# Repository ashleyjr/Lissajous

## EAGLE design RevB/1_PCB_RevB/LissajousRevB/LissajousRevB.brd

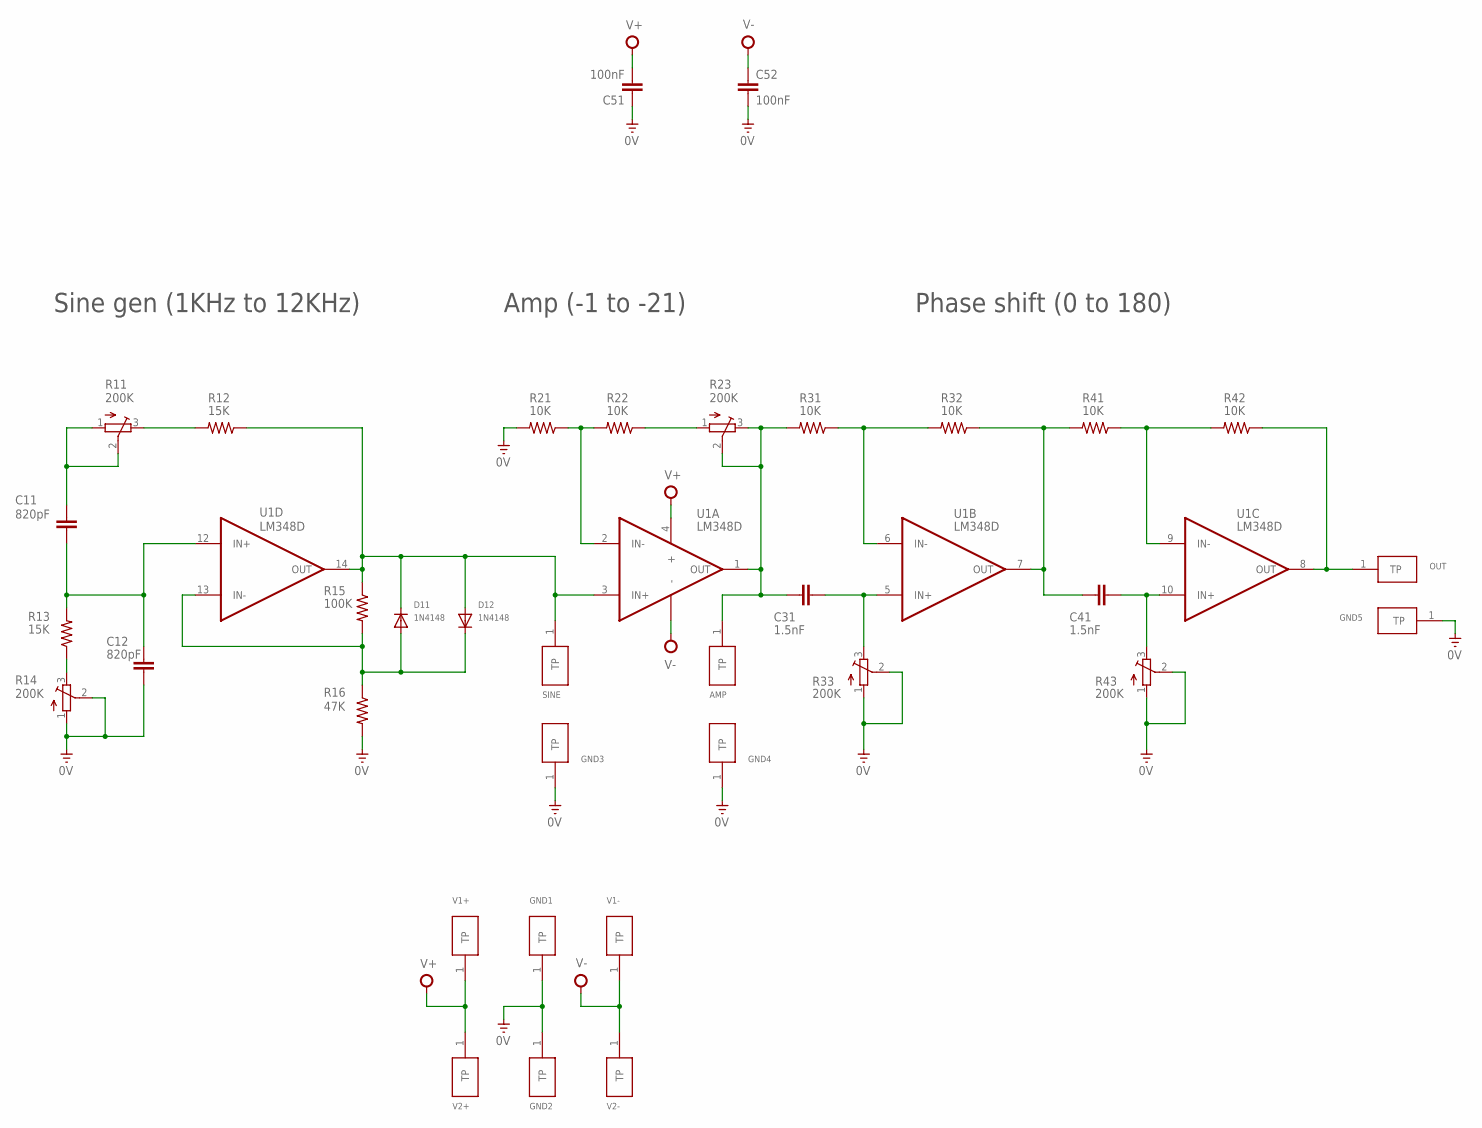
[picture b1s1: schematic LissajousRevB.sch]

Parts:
AMP: TESTPADS; TEST
C11, C12: 820pF; 0603-CAP
C31, C41: 1.5nF; 0603-CAP
C51, C52: 100nF; 0603-CAP
D11, D12: 1N4148; SMADIODE
GND1, GND2, GND3, GND4, GND5: TESTPADS; TEST
OUT: TESTPADS; TEST
R11, R14, R23, R33, R43: 200K; TC33X
R12, R13: 15K; 0603-RES
R15: 100K; 0603-RES
R16: 47K; 0603-RES
R21, R22, R31, R32, R41, R42: 10K; 0603-RES
SINE: TESTPADS; TEST
U1: LM348D; SOIC127P600X175-14N
V1+, V1-, V2+, V2-: TESTPADS; TEST

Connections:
0V: C12.1, C51.1, C52.2, GND1.1, GND2.1, GND3.1, GND4.1, GND5.1, R14.1 (A), R14.2 (S), R16.2, R21.2, R33.1 (A), R33.2 (S), R43.1 (A), R43.2 (S)
unnamed: R11.3 (E), R12.2
unnamed: R13.1, R14.3 (E)
unnamed: D11.A, D12.C, R15.2, R16.1, U1.13 (IN-)
unnamed: C11.2, R11.1 (A), R11.2 (S)
unnamed: R22.1, R23.1 (A)
unnamed: C11.1, C12.2, R13.2, U1.12 (IN+)
unnamed: R21.1, R22.2, U1.2 (IN-)
unnamed: R31.1, R32.2, U1.6 (IN-)
unnamed: C31.1, R33.3 (E), U1.5 (IN+)
unnamed: AMP.1, C31.2, R23.2 (S), R23.3 (E), R31.2, U1.1 (OUT)
unnamed: R41.1, R42.2, U1.9 (IN-)
unnamed: C41.1, R43.3 (E), U1.10 (IN+)
unnamed: OUT.1, R42.1, U1.8 (OUT)
unnamed: C41.2, R32.1, R41.2, U1.7 (OUT)
SINE: D11.C, D12.A, R12.1, R15.1, SINE.1, U1.3 (IN+), U1.14 (OUT)
V+: C51.2, U1.4 (+), V1+.1, V2+.1
V-: C52.1, U1.11 (-), V1-.1, V2-.1

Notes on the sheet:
Sine gen (1KHz to 12KHz)
Amp (-1 to -21)
Phase shift (0 to 180)

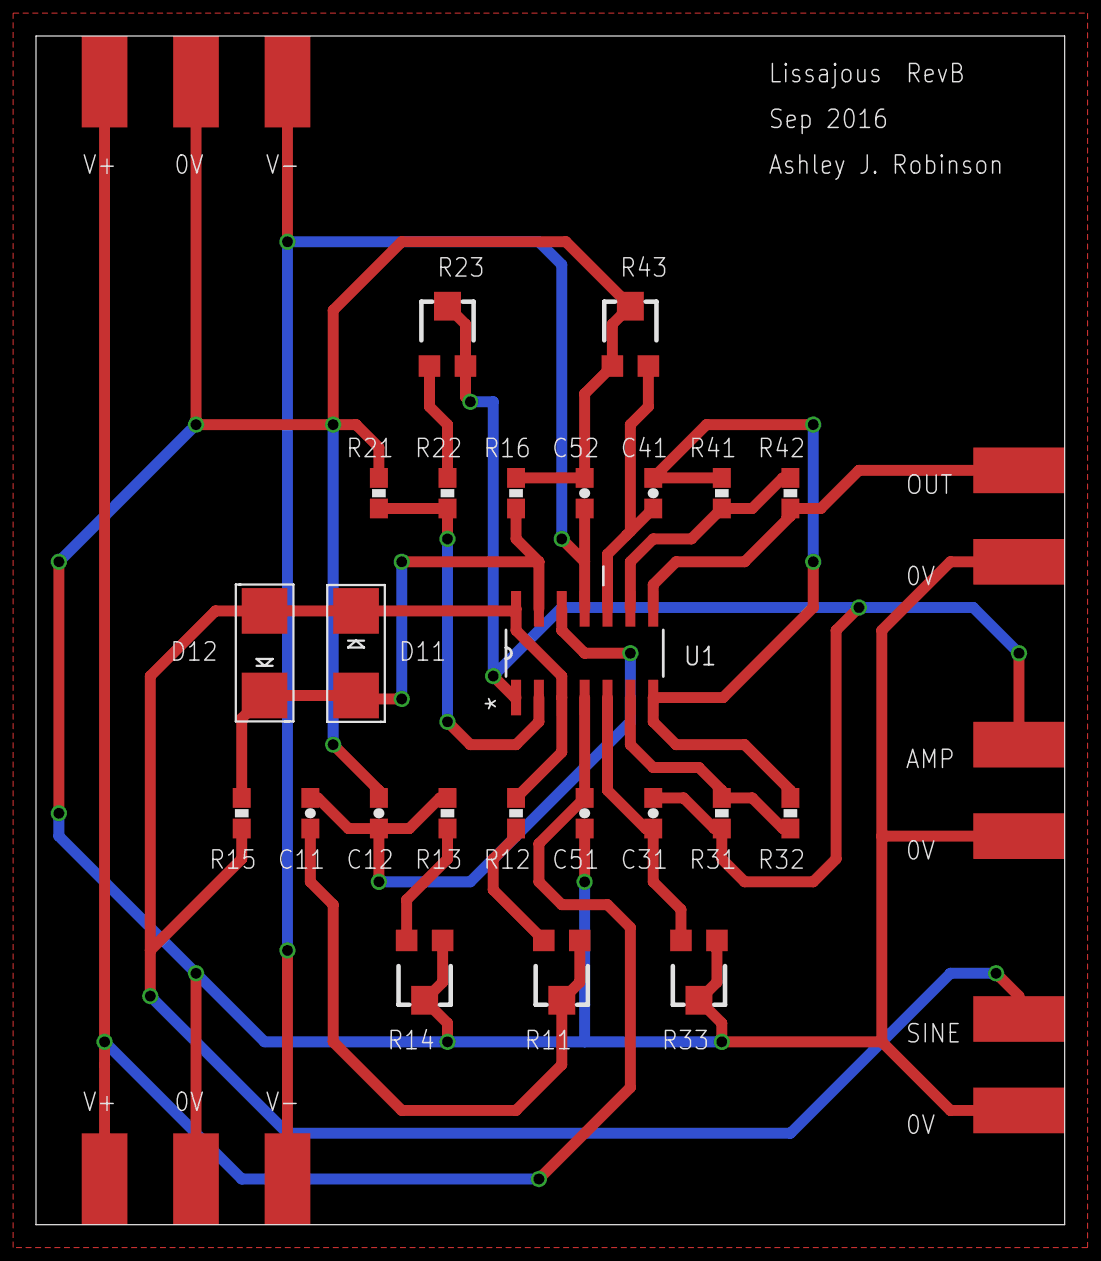
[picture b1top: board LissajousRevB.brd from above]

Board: 2 copper layers, 57.1 x 66.0 mm, 36 parts (0 on the bottom side), 18 nets.

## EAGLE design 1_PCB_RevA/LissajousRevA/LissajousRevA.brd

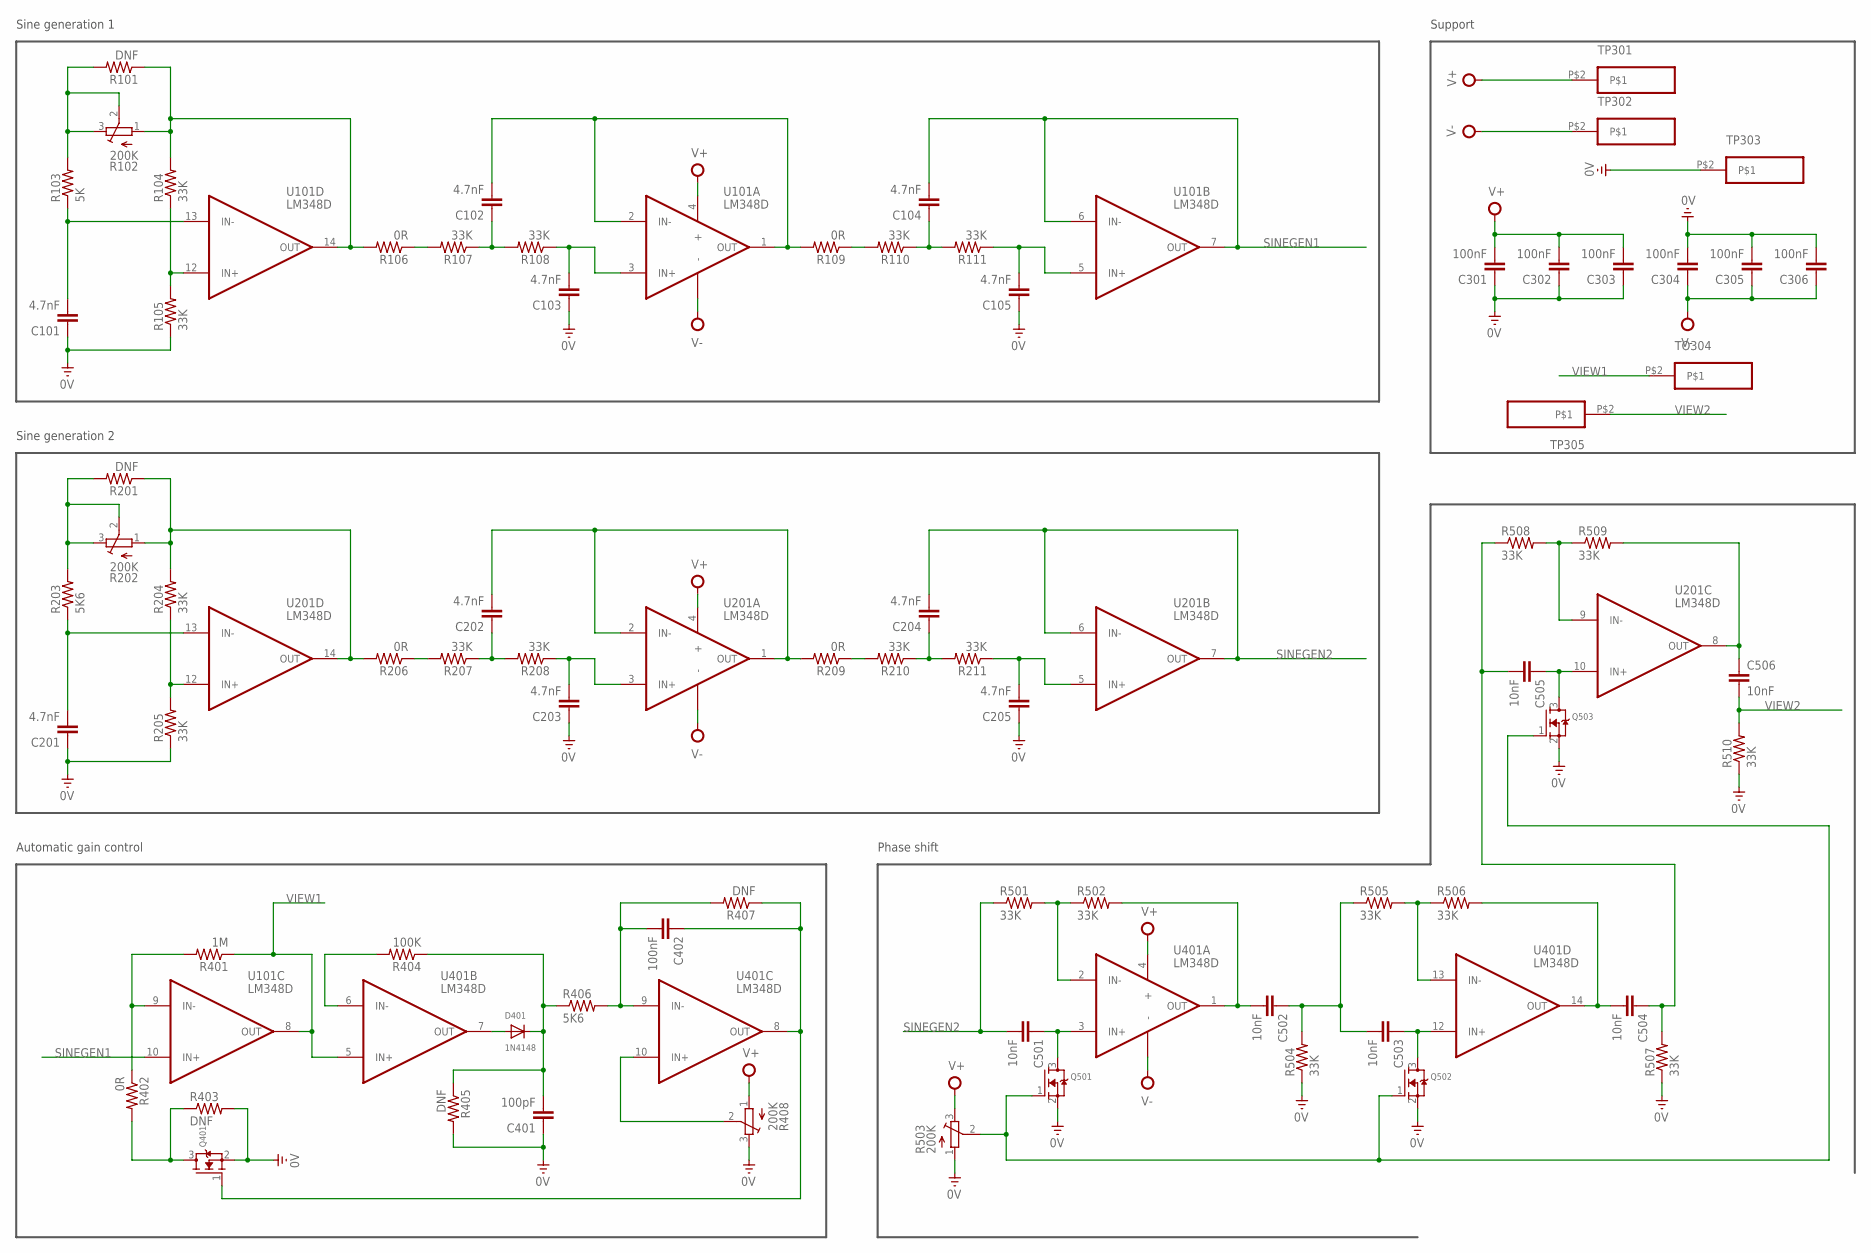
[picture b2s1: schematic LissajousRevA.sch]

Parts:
C101, C102, C103, C104, C105, C201, C202, C203, C204, C205: 4.7nF; 0603-CAP
C301, C302, C303, C304, C305, C306, C402: 100nF; 0603-CAP
C401: 100pF; 0603-CAP
C501, C502, C503, C504, C505, C506: 10nF; 0603-CAP
D401: 1N4148; SMADIODE
Q401, Q501, Q502, Q503: MOSFET-NREFLOW; SOT23
R101, R201, R403, R405, R407: DNF; 0603-RES
R102, R202, R408, R503: 200K; TC33X
R103: 5K; 0603-RES
R104, R105, R107, R108, R110, R111, R204, R205, R207, R208, R210, R211, R501, R502, R504, R505, R506, R507, R508, R509, R510: 33K; 0603-RES
R106, R109, R206, R209, R402: 0R; 0603-RES
R203, R406: 5K6; 0603-RES
R401: 1M; 0603-RES
R404: 100K; 0603-RES
TO304: PAD
TP301, TP302, TP303, TP305: PAD
U101, U201, U401: LM348D; SOIC127P600X175-14N

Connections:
0V: C101.1, C103.1, C105.1, C201.1, C203.1, C205.1, C301.1, C302.1, C303.1, C304.2, C305.2, C306.2, C401.1, Q401.2 (S), Q501.2 (S), Q502.2 (S), Q503.2 (S), R105.1, R205.1, R403.2, R405.2, R408.3 (E), R503.1 (A), R504.1, R507.1, R510.1, TP303.P$2
unnamed: C101.2, R103.1, U101.13 (IN-)
unnamed: R104.1, R105.2, U101.12 (IN+)
unnamed: R106.1, R107.2
unnamed: R101.2, R102.2 (S), R102.3 (E), R103.2
unnamed: C103.2, R108.1, U101.3 (IN+)
unnamed: C102.1, R107.1, R108.2
unnamed: R101.1, R102.1 (A), R104.2, R106.2, U101.14 (OUT)
unnamed: C102.2, R109.2, U101.1 (OUT), U101.2 (IN-)
unnamed: R204.1, R205.2, U201.12 (IN+)
unnamed: C201.2, R203.1, U201.13 (IN-)
unnamed: C105.2, R111.1, U101.5 (IN+)
unnamed: C104.1, R110.1, R111.2
unnamed: R401.2, R402.1, U101.9 (IN-)
unnamed: R109.1, R110.2
unnamed: R201.1, R202.1 (A), R204.2, R206.2, U201.14 (OUT)
unnamed: C203.2, R208.1, U201.3 (IN+)
unnamed: C202.1, R207.1, R208.2
unnamed: C205.2, R211.1, U201.5 (IN+)
unnamed: C204.1, R210.1, R211.2
unnamed: C501.1, Q501.3 (D), U401.3 (IN+)
unnamed: C202.2, R209.2, U201.1 (OUT), U201.2 (IN-)
unnamed: R206.1, R207.2
unnamed: R209.1, R210.2
unnamed: R201.2, R202.2 (S), R202.3 (E), R203.2
unnamed: C402.2, R406.2, R407.2, U401.9 (IN-)
unnamed: R501.2, R502.1, U401.2 (IN-)
unnamed: R404.2, U401.6 (IN-)
unnamed: D401.A, U401.7 (OUT)
unnamed: C502.1, C503.2, R504.2, R505.1
unnamed: C401.2, D401.C, R404.1, R405.1, R406.1
unnamed: Q401.3 (D), R402.2, R403.1
unnamed: C402.1, Q401.1 (G), R407.1, U401.8 (OUT)
unnamed: C502.2, R502.2, U401.1 (OUT)
unnamed: R408.2 (S), U401.10 (IN+)
unnamed: C503.1, Q502.3 (D), U401.12 (IN+)
unnamed: R505.2, R506.1, U401.13 (IN-)
unnamed: Q501.1 (G), Q502.1 (G), Q503.1 (G), R503.2 (S)
unnamed: C504.2, R506.2, U401.14 (OUT)
unnamed: R508.2, R509.1, U201.9 (IN-)
unnamed: C504.1, C505.2, R507.2, R508.1
unnamed: C505.1, Q503.3 (D), U201.10 (IN+)
unnamed: C506.1, R509.2, U201.8 (OUT)
SINEGEN1: C104.2, U101.6 (IN-), U101.7 (OUT), U101.10 (IN+)
SINEGEN2: C204.2, C501.2, R501.1, U201.6 (IN-), U201.7 (OUT)
V+: C301.2, C302.2, C303.2, R408.1 (A), R503.3 (E), TP301.P$2, U101.4 (+), U201.4 (+), U401.4 (+)
V-: C304.1, C305.1, C306.1, TP302.P$2, U101.11 (-), U201.11 (-), U401.11 (-)
VIEW1: R401.1, TO304.P$2, U101.8 (OUT), U401.5 (IN+)
VIEW2: C506.2, R510.2, TP305.P$2

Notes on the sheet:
Sine generation 1
Sine generation 2
Support
Automatic gain control
Phase shift

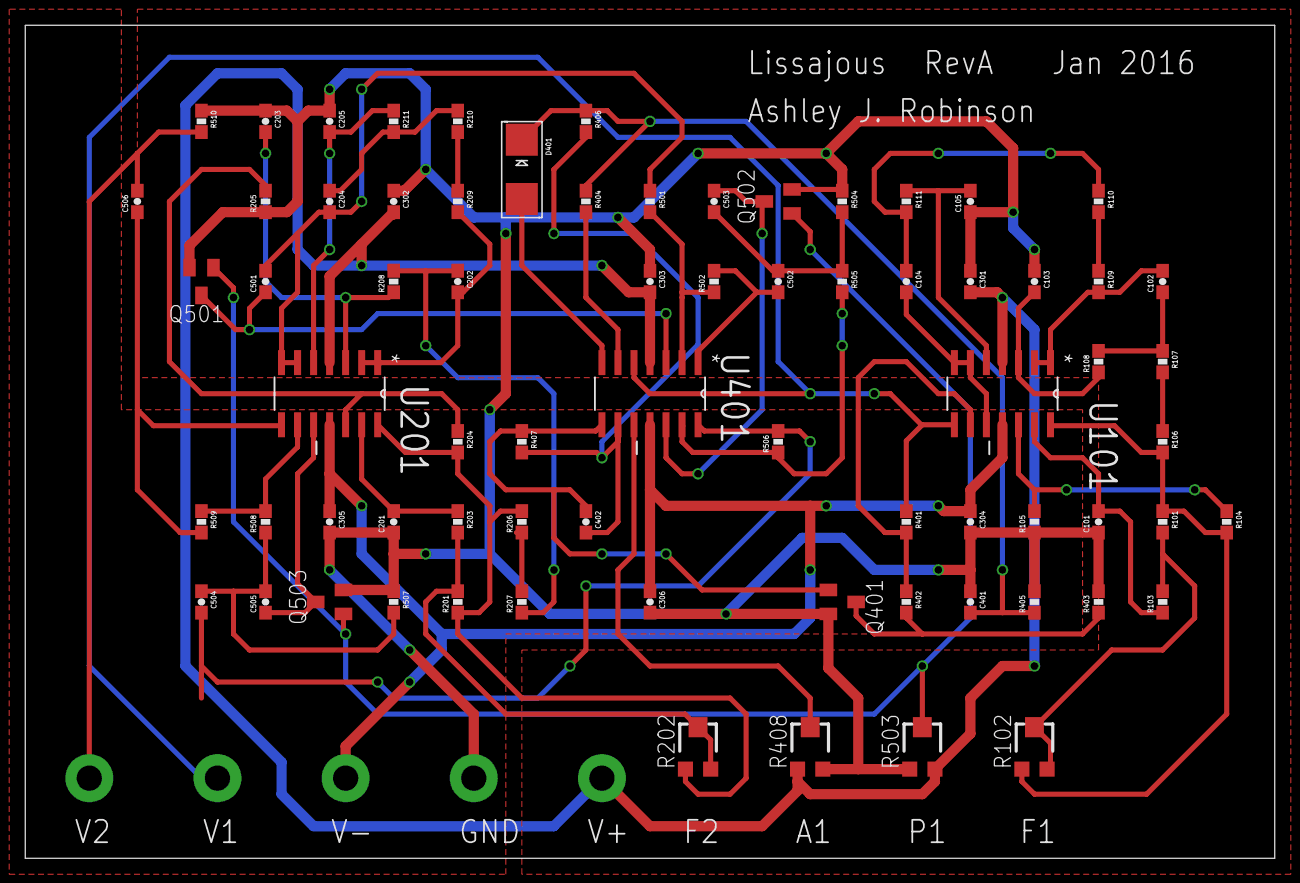
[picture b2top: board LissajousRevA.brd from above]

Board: 2 copper layers, 99.1 x 66.0 mm, 77 parts (0 on the bottom side), 49 nets.

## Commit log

2015-12-02 two phase shift sims
2015-12-03 added rc on front of opamp
2015-12-03 double phase shift
2015-12-04 fet shifter circuit
2015-12-10 fet shift change
2015-12-10 added phase detector
2015-12-10 put detect on end
2015-12-10 experiment with freq
2015-12-12 added lpf on output to offset
2015-12-12 idea image aded
2015-12-12 experiment with phase shift oscillator
2015-12-14 negative resistance
2015-12-15 experiment with varactor diode
2015-12-19 new approach in time for xmas deliver
2015-12-20 first attempt at plugging together agc
2015-12-20 sort of working?
2015-12-21 working well, proved enough to tune when built
2015-12-23 added multi part 348 soic op amp
2015-12-24 first relax osc and lpf
2015-12-24 added second gen
2015-12-24 schmatics have everything down
2015-12-24 schematic capture done
2015-12-24 initital placment
2015-12-29 sch net fix and more placement
2015-12-29 lots of routing and another net fix
2015-12-29 removed test points, can just use legs instead
2015-12-29 nearly fully routed, lots tp optimise though
2015-12-31 project file
2015-12-31 lots of lceaning up from a fully connected layout, accidental full commit, need to clean
2015-12-31 remove unwanted
2016-01-01 quick route
2016-01-02 layout in bottom left
2016-01-03 more sparse routing
2016-01-03 fully routed and pass board house drc
2016-01-03 more layout opt
2016-01-04 bring test points to bottom of pcb
2016-01-07 added bigger test pads to pcb
2016-01-07 begin to opt power rail
2016-01-09 Added silk and tidy up tracks
2016-01-09 flood and final tidy
2016-01-09 added drill legend
2016-01-09 overlap and moved designator on ICs
2016-01-09 fix text as it changes to vector
2016-01-09 created gerbers
2016-01-09 order out
2016-02-13 added bom export tool and exported bom
2016-02-13 Added component order from farnell
2016-04-22 data and images from build and test
2016-04-29 Tested sine gen 2 and it works
2016-08-22 start fixing issues with Rev A
2016-08-25 sweep of sine wave gen
2016-08-25 test of filter
2016-08-25 try to fix filter output
2016-09-20 new oscillator
2016-09-20 all pass filter
2016-09-21 restructure for Rev B
2016-09-21 remove old files
2016-09-21 copy over Rev B files
2016-09-21 chnage file name
2016-09-21 sheet to sweep oscillator
2016-09-24 down to one quad op-amp package
2016-09-24 core schematics done
2016-09-24 ready to route
2016-09-24 initial placement
2016-09-24 first pass at routing
2016-09-24 ready to gen gerbers
2016-09-24 data out
2016-11-02 order for components placed

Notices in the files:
parts and their libraries:
passives: Licensing: Creative Commons ShareAlike 4.0 International - https://creativecommons.org/licenses/by-sa/4.0
